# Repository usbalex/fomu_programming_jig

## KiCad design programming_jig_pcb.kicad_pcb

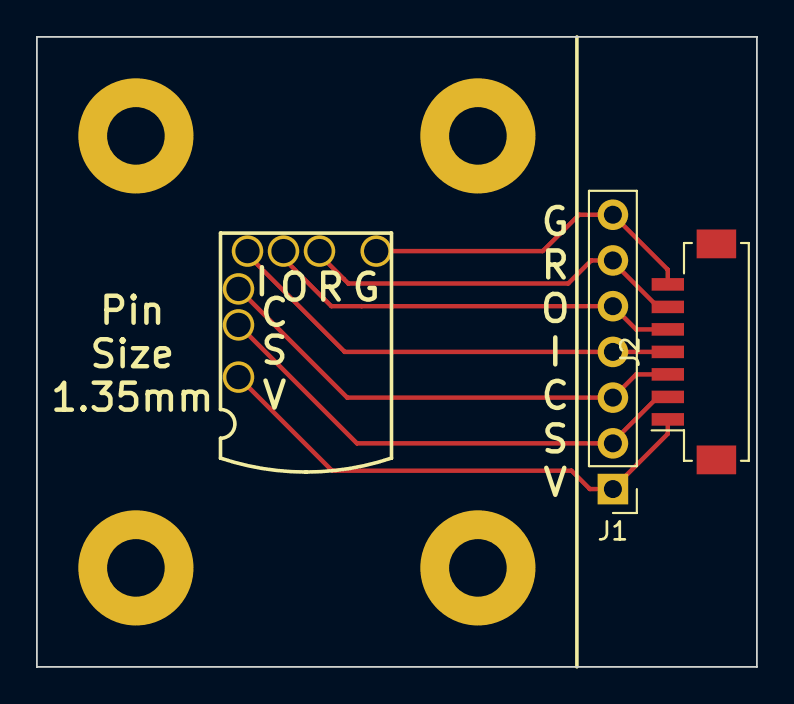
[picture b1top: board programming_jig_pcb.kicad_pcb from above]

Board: 2 copper layers, 40.0 x 35.0 mm, 13 parts (0 on the bottom side), 7 nets.

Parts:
C: TestPoint_Probe; PogoPin_1.37mm
G: TestPoint_Probe; PogoPin_1.37mm
H1, H2, H3, H4: MountingHole; MountingHole_3.2mm_M3_Pad
I: TestPoint_Probe; PogoPin_1.37mm
J1: Conn_01x07_Male; PinHeader_1x07_P2.54mm_Vertical
J2: Conn_01x07_Male; Hirose_DF13C_CL535-0407-6-51_1x07-1MP_P1.25mm_Vertical
O: TestPoint_Probe; PogoPin_1.37mm
R: TestPoint_Probe; PogoPin_1.37mm
S: TestPoint_Probe; PogoPin_1.37mm
V: TestPoint_Probe; PogoPin_1.37mm

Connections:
unnamed: J1.1, J2.1, V.1
unnamed: J1.2, J2.2, S.1
unnamed: C.1, J1.3, J2.3
unnamed: I.1, J1.4, J2.4
unnamed: J1.5, J2.5, O.1
unnamed: J1.6, J2.6, R.1
unnamed: G.1, J1.7, J2.7

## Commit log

2019-09-13 Initial commit
    Prototype PCB designs for building up a FOMU programming jig.
